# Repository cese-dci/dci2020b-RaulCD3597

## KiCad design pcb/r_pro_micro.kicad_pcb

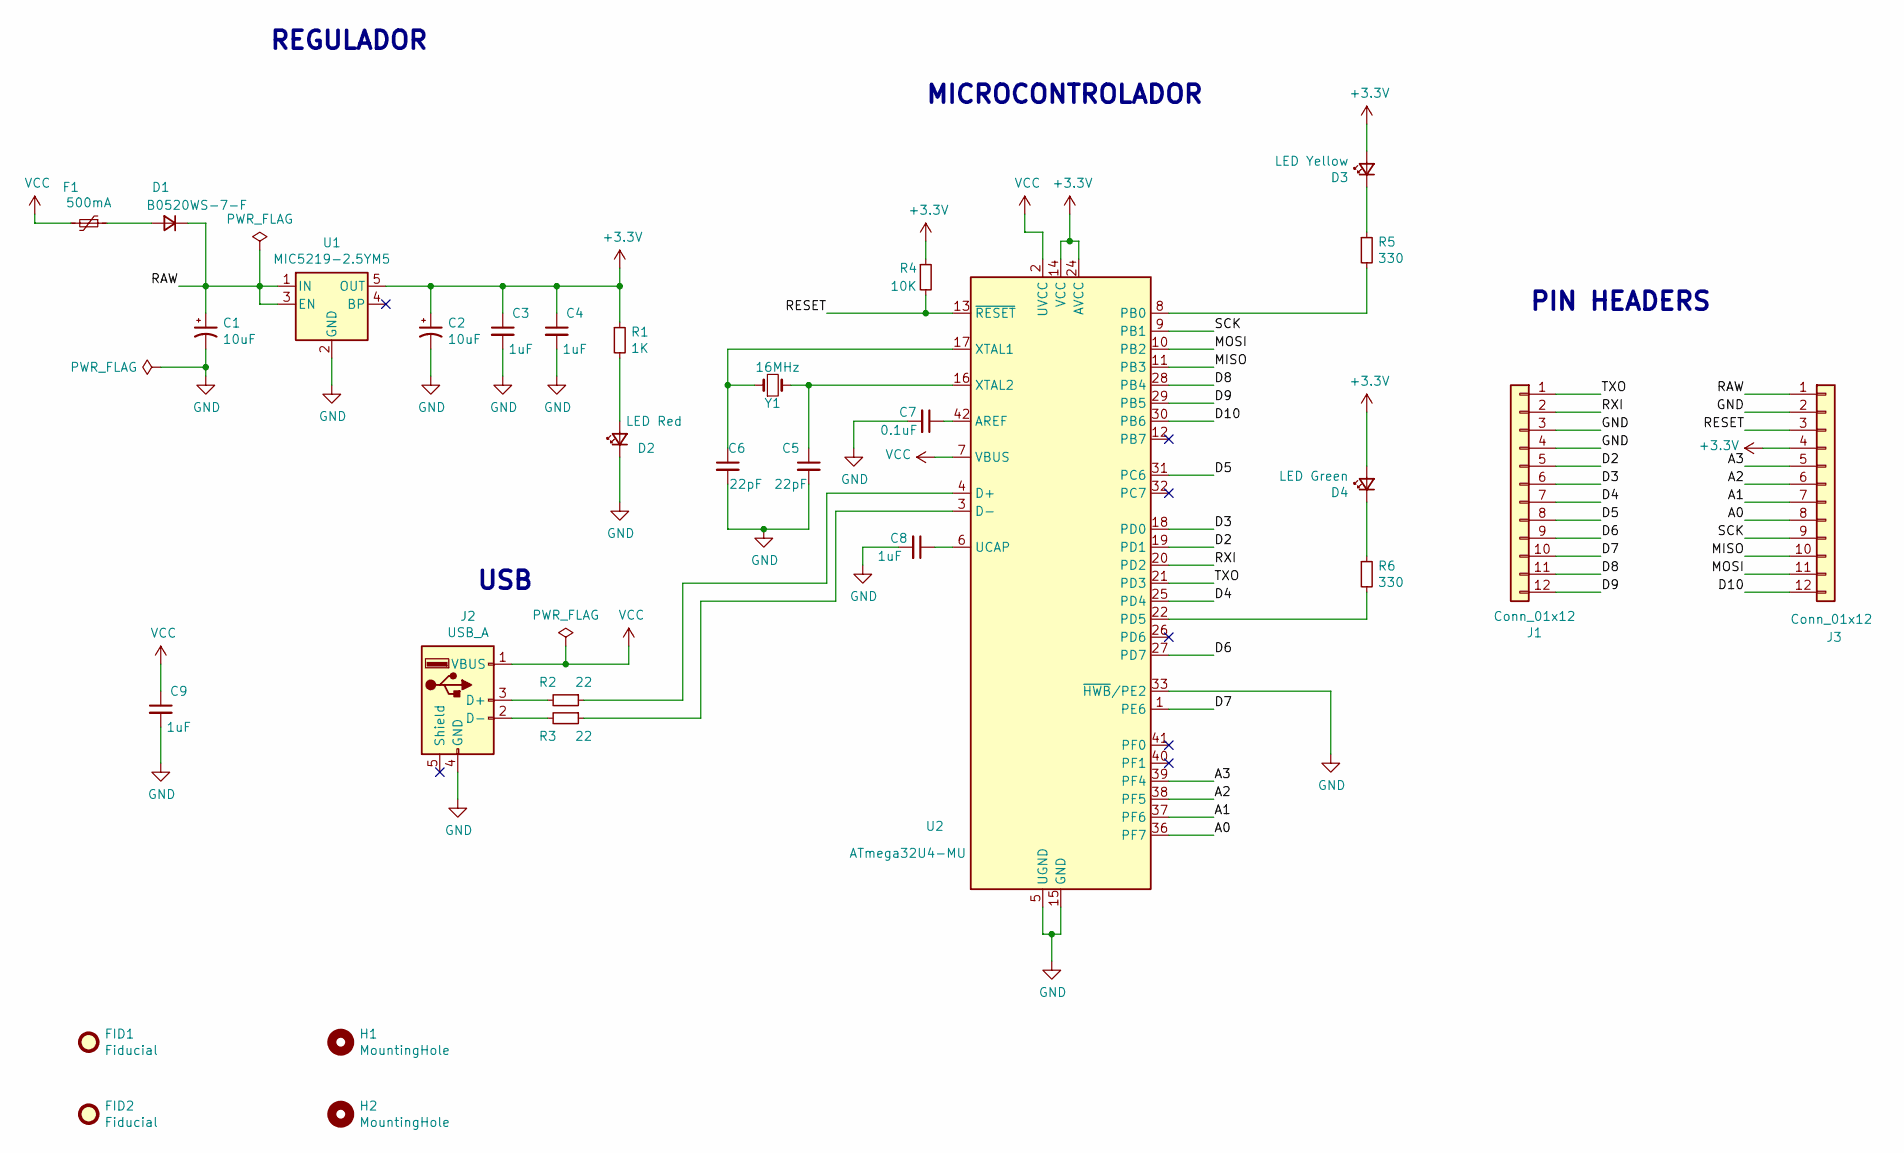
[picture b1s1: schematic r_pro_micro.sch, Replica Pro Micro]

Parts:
C1, C2: 10uF; CP_EIA-3216-10_Kemet-I
C3, C4, C8, C9: 1uF; C_0805_2012Metric
C5, C6: 22pF; C_0805_2012Metric
C7: 0.1uF; C_0805_2012Metric
D1: B0520WS-7-F; D_SOD-523; MFG# B0520WS-7-F
D2: LED Red; LED_0805_2012Metric
D3: LED Yellow; LED_0805_2012Metric
D4: LED Green; LED_0805_2012Metric
F1: 500mA; Fuse_1206_3216Metric; MFG# 0ZCG0050AF2C
FID1, FID2: Fiducial; Fiducial_0.5mm_Mask1mm
H1, H2: MountingHole; MountingHole_2.1mm
J1, J3: Conn_01x12; PinHeader_1x12_P2.54mm_Vertical; MFG# PEC12SACN
J2: USB_A; USB_Micro-B_Molex_47346-0001; MFG# 0475890001
R1: 1K; R_0805_2012Metric
R2, R3: 22; R_0805_2012Metric
R4: 10K; R_0805_2012Metric
R5, R6: 330; R_0805_2012Metric
U1: MIC5219-2.5YM5; SOT-23-5; MFG# MIC5219-2.85BMM-TR
U2: ATmega32U4-MU; QFN-44-1EP_7x7mm_P0.5mm_EP5.2x5.2mm; MFG# ATMEGA32U4-MU
Y1: 16MHz; Crystal_SMD_3225-4Pin_3.2x2.5mm

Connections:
+3V3: C2.1, C3.1, C4.1, D3.2 (A), D4.2 (A), J3.4, R1.1, R4.1, U1.5 (OUT), U2.14 (VCC), U2.24 (AVCC), U2.34 (VCC), U2.44 (AVCC)
/A0: J3.8, U2.36 (PF7)
/A1: J3.7, U2.37 (PF6)
/A2: J3.6, U2.38 (PF5)
/A3: J3.5, U2.39 (PF4)
/D2: J1.5, U2.19 (PD1)
/D3: J1.6, U2.18 (PD0)
/D4: J1.7, U2.25 (PD4)
/D5: J1.8, U2.31 (PC6)
/D6: J1.9, U2.27 (PD7)
/D7: J1.10, U2.1 (PE6)
/D8: J1.11, U2.28 (PB4)
/D9: J1.12, U2.29 (PB5)
/D10: J3.12, U2.30 (PB6)
/MISO: J3.10, U2.11 (PB3)
/MOSI: J3.11, U2.10 (PB2)
/RAW: C1.1, D1.1 (K), J3.1, U1.1 (IN), U1.3 (EN)
/RESET: J3.3, R4.2, U2.13 (~RESET)
/RXI: J1.2, U2.20 (PD2)
/SCK: J3.9, U2.9 (PB1)
/TXO: J1.1, U2.21 (PD3)
GND: C1.2, C2.2, C3.2, C4.2, C5.2, C6.2, C7.2, C8.2, C9.2, D2.1 (K), J1.3, J1.4, J2.4 (GND), J3.2, U1.2 (GND), U2.5 (UGND), U2.15 (GND), U2.23 (GND), U2.33 (~HWB~/PE2), U2.35 (GND), U2.43 (GND), U2.45 (GND)
unnamed: C5.1, U2.16 (XTAL2), Y1.2
unnamed: C6.1, U2.17 (XTAL1), Y1.1
unnamed: C7.1, U2.42 (AREF)
unnamed: C8.1, U2.6 (UCAP)
unnamed: D1.2 (A), F1.1
unnamed: D2.2 (A), R1.2
unnamed: D3.1 (K), R5.1
unnamed: D4.1 (K), R6.1
unnamed: J2.2 (D-), R3.2
unnamed: J2.3 (D+), R2.2
unnamed: R2.1, U2.4 (D+)
unnamed: R3.1, U2.3 (D-)
unnamed: R5.2, U2.8 (PB0)
unnamed: R6.2, U2.22 (PD5)
VCC: C9.1, F1.2, J2.1 (VBUS), U2.2 (UVCC), U2.7 (VBUS)

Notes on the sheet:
PIN HEADERS
USB
MICROCONTROLADOR
REGULADOR

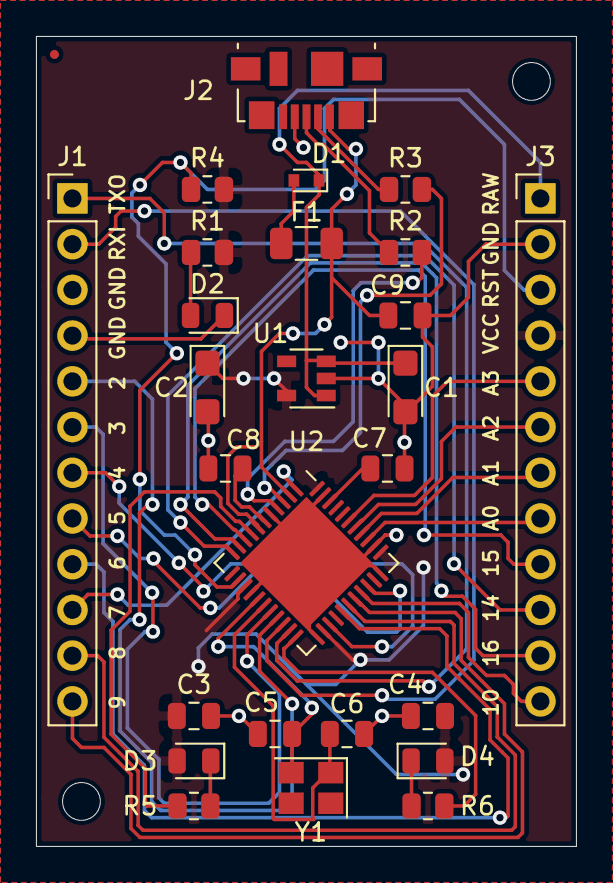
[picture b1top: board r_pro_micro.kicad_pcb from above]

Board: 2 copper layers, 30.0 x 45.0 mm, 30 parts (1 on the bottom side), 37 nets.

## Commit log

2020-09-18 ** Primer commit **
2020-10-08 ** Se agregan footprints **
2020-10-08 ** Se crea netlist cambiando R 0omhs por nettie **
2020-10-10 ** Se modifica etiquetas y disposicion del esquematico **
2020-10-10 ** Se cambian huellas a 0805 **
2020-10-11 ** Se corrige rotulo esquematico **
2020-10-11 ** Importacion de netlist en pcb
2020-10-12 ** Se realiza posicionamiento de footprints **
2020-10-12 ** Se corrige posicionamiento **
2020-10-16 ** e agrega informacion de digikey en componentes importantes **
2020-10-22 ** Se rehace posicionamiento de footprints **
2020-10-23 ** Se hace completa el ruteo
2020-10-24 Se reahace PCB
2020-10-24 Se agrega notas en PCB
2020-10-24 ** Se suben modelos 3D del proyecto **

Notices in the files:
pcb/r_pro_micro.kicad_pcb:
Bajo licencia Creative Commons Attribution Share - Alike 4.0
pcb/r_pro_micro.sch:
https://creativecommons.org/licenses/by-sa/4.0
